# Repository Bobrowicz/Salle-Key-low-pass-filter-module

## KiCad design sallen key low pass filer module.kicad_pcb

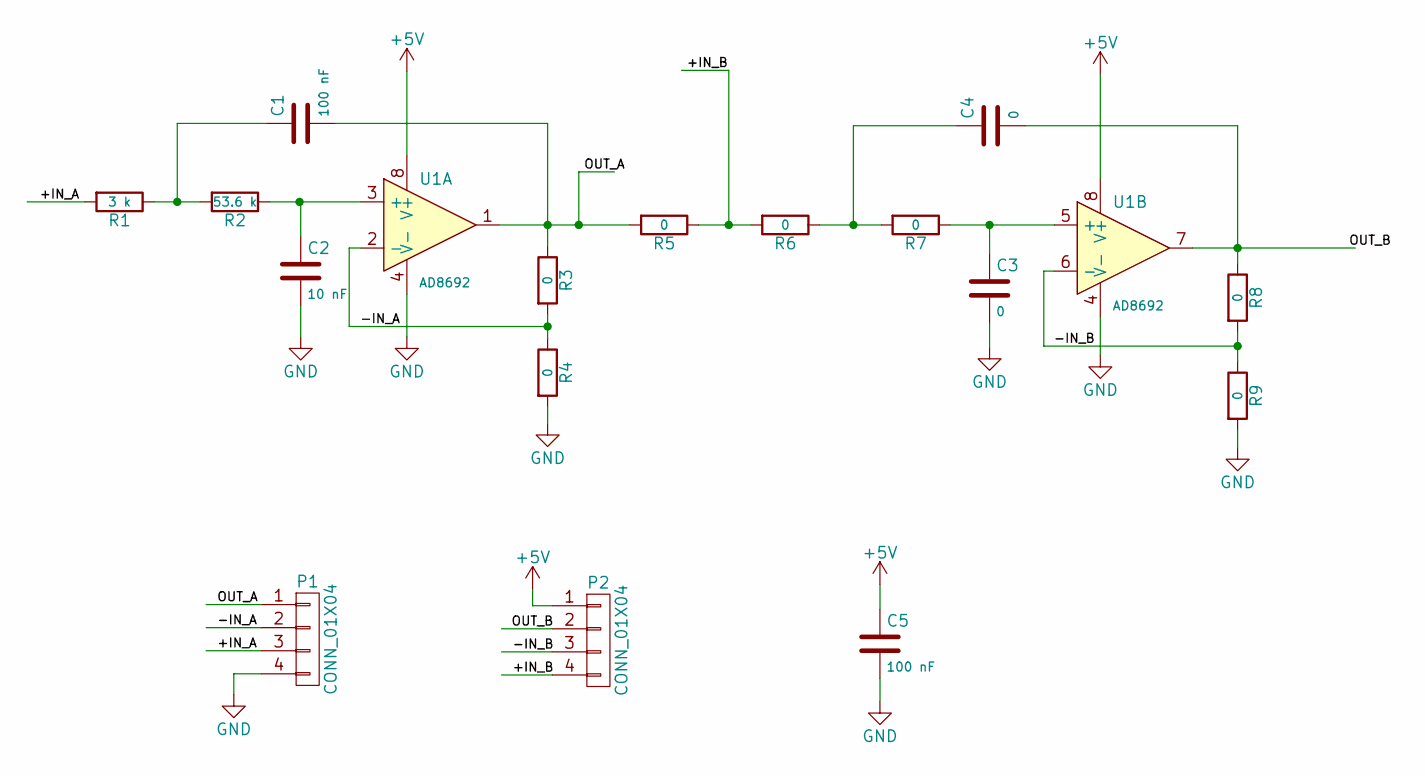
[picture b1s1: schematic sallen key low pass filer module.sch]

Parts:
C1, C5: 100 nF; C_0805_HandSoldering
C2: 10 nF; C_0805_HandSoldering
C3, C4: 0; C_0805_HandSoldering
P1, P2: CONN_01X04; Pin_Header_Straight_1x04_Pitch2.54mm
R1: 3 k; R_0805_HandSoldering
R2: 53.6 k; R_0805_HandSoldering
R3, R4, R5, R6, R7, R8, R9: 0; R_0805_HandSoldering
U1: AD8692; SOIC-8-N

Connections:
+5V: C5.1, P2.1, U1.8 (V+)
/+IN_A: P1.3, R1.2
/+IN_B: P2.4, R5.1, R6.2
/-IN_A: P1.2, R3.2, R4.1, U1.2 (-)
/-IN_B: P2.3, R8.2, R9.1, U1.6 (-)
/OUT_A: C1.2, P1.1, R3.1, R5.2, U1.1
/OUT_B: C4.2, P2.2, R8.1, U1.7
GND: C2.2, C3.2, C5.2, P1.4, R4.2, R9.2, U1.4 (V-)
unnamed: C1.1, R1.1, R2.2
unnamed: C2.1, R2.1, U1.3 (+)
unnamed: C3.1, R7.1, U1.5 (+)
unnamed: C4.1, R6.1, R7.2

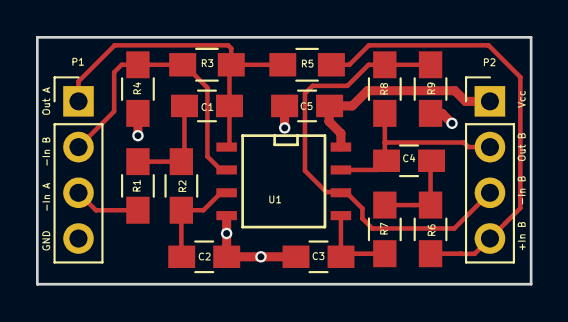
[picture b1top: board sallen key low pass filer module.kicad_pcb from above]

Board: 2 copper layers, 27.4 x 13.7 mm, 17 parts (0 on the bottom side), 12 nets.

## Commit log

2018-08-09 :tada: Added .gitattributes & .gitignore files
2018-08-10 silk screen edits
